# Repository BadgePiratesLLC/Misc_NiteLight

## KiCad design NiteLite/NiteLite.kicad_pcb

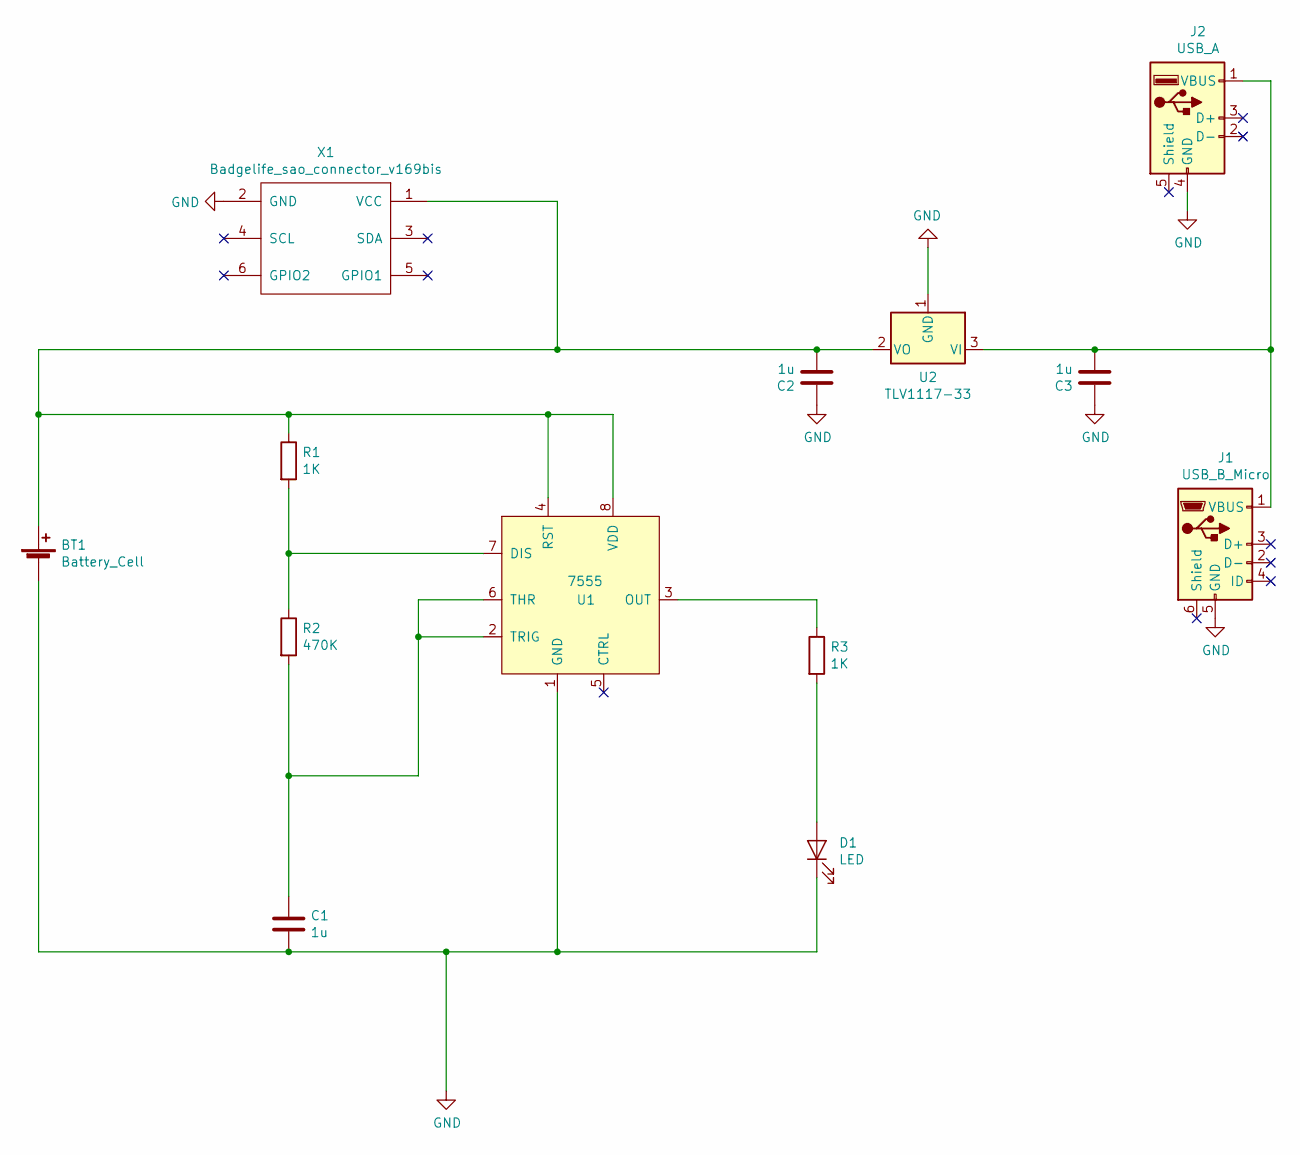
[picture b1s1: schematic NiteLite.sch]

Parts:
BT1: Battery_Cell; BatteryHolder_MPD_BC2003_1x2032
C1, C2, C3: 1u; C_0805_2012Metric_Pad1.15x1.40mm_HandSolder
D1: LED; LED_1206_3216Metric_Pad1.42x1.75mm_HandSolder
J1: USB_B_Micro; USB_Micro-B_Wuerth_629105150521
J2: USB_A; USB_A_CNCTech_1001-011-01101_Horizontal
R1, R3: 1K; R_1206_3216Metric_Pad1.42x1.75mm_HandSolder
R2: 470K; R_1206_3216Metric_Pad1.42x1.75mm_HandSolder
U1: 7555; SOIC-8-1EP_3.9x4.9mm_P1.27mm_EP2.514x3.2mm
U2: TLV1117-33; SOT-223
X1: Badgelife_sao_connector_v169bis; Badgelife-SAOv169-BADGE-2x3

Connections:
GND: BT1.2 (-), C1.2, C2.1, C3.1, D1.1 (K), J1.5 (GND), J2.4 (GND), U1.1 (GND), U2.1 (GND), X1.2 (GND)
unnamed: BT1.1 (+), C2.2, R1.1, U1.4 (RST), U1.8 (VDD), U2.2 (VO), X1.1 (VCC)
unnamed: C1.1, R2.2, U1.2 (TRIG), U1.6 (THR)
unnamed: C3.2, J1.1 (VBUS), J2.1 (VBUS), U2.3 (VI)
unnamed: D1.2 (A), R3.2
unnamed: R1.2, R2.1, U1.7 (DIS)
unnamed: R3.1, U1.3 (OUT)

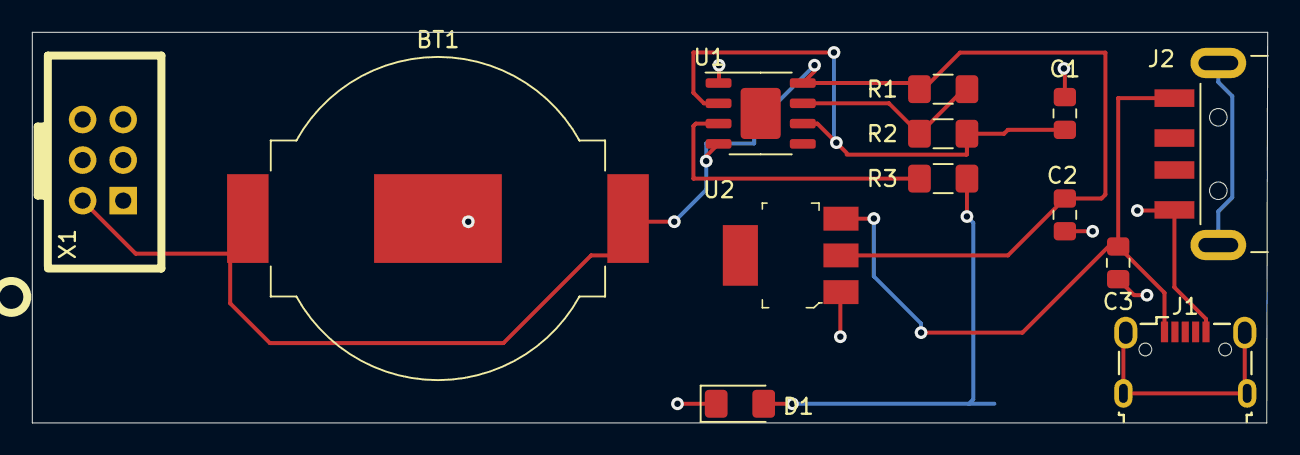
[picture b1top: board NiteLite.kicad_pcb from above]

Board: 2 copper layers, 77.4 x 24.5 mm, 13 parts (0 on the bottom side), 7 nets.

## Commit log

2020-08-28 updates to artwork and sch
